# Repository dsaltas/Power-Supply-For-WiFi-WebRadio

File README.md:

## Power Supply For WiFi WebRadio

This is a miniature power supply with built-in Li-Ion charger for [WiFi WebRadio](https://github.com/dsaltas/WiFi-WebRadio).

It is based on [LTC3440](https://www.analog.com/en/products/ltc3440.html) chip. A Micropower Synchronous Buck-Boost DC/DC Converter.

### Features

- Voltage input 2,7V to 4,2V
- Voltage output 3,3V at 600mA
- Low battery LED indicator at 3V or less
- Li-Ion charger at 4,2V / 500mA

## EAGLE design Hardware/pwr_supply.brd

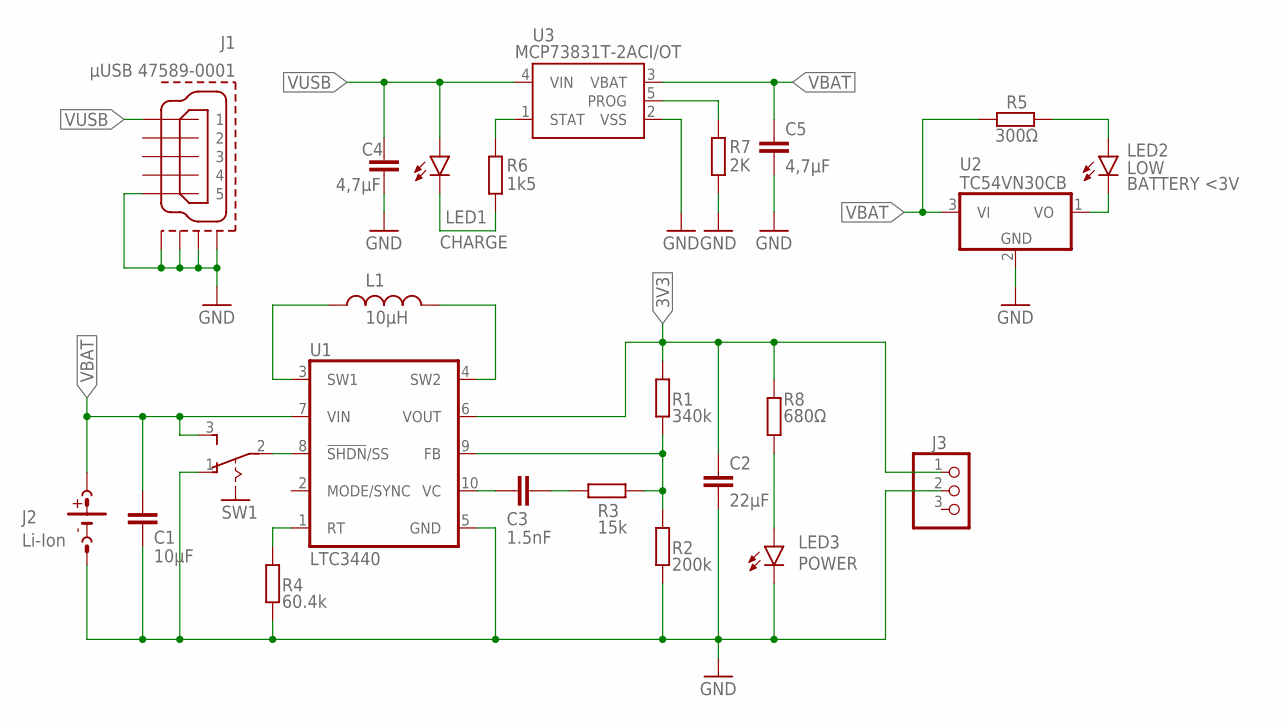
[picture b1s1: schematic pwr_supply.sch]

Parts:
C1: 10μF; C0805
C2: 22μF; C1210
C3: 1.5nF; C0805
C4, C5: 4,7μF; C0805
J1: μUSB 47589-0001; 47589-0001
J2: Li-Ion; JSTPH2
J3: PINHD-1X3/90; 1X03/90
L1: 10μH; CDRH6D38
LED1: CHARGE; CHIPLED_0805
LED2: LOW; CHIPLED_0805
LED3: POWER; CHIPLED_0805
R1: 340k; R0805
R2: 200k; R0805
R3: 15k; R0805
R4: 60.4k; R0805
R5: 300Ω; R0805
R6: 1k5; R0805
R7: 2K; R0805
R8: 680Ω; R0805
SW1: JS102011SAQN
U1: LTC3440; MSOP10
U2: TC54VN30CB; SOT23
U3: MCP73831T-2ACI/OT; SOT23-5

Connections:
3V3: C2.1, J3.1, R1.2, R8.2, U1.6 (VOUT)
GND: C1.2, C2.2, C4.2, C5.2, J1.5, J1.CASING1 (GND1), J1.CASING2 (GND2), J1.CASING3 (GND3), J1.CASING4 (GND4), J2.1 (-), J3.2, LED3.C, R2.1, R4.1, R7.1, SW1.1 (O), U1.5 (GND), U2.2 (GND), U3.2 (VSS)
unnamed: R4.2, U1.1 (RT)
unnamed: LED2.A, R5.1
unnamed: L1.1, U1.3 (SW1)
unnamed: L1.2, U1.4 (SW2)
unnamed: C3.1, U1.10 (VC)
unnamed: C3.2, R3.1
unnamed: R1.1, R2.2, R3.2, U1.9 (FB)
unnamed: SW1.2, U1.8 (!SHDN!/SS)
unnamed: LED2.C, U2.1 (VO)
unnamed: R7.2, U3.5 (PROG)
unnamed: R6.2, U3.1 (STAT)
unnamed: LED1.C, R6.1
unnamed: LED3.A, R8.1
VBAT: C1.1, C5.1, J2.2 (+), R5.2, SW1.3 (S), U1.7 (VIN), U2.3 (VI), U3.3 (VBAT)
VUSB: C4.1, J1.1, LED1.A, U3.4 (VIN)

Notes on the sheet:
BATTERY <3V

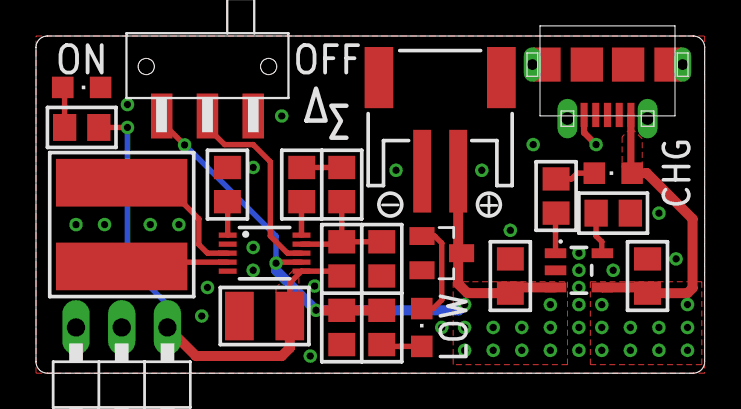
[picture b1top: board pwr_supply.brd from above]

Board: 2 copper layers, 37.1 x 18.7 mm, 24 parts (0 on the bottom side), 17 nets.

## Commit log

2020-03-13 Create test
2021-04-26 Bill of Materials
2021-04-26 Create keep

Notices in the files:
Hardware/pwr_supply.brd:
© 2019
parts and their libraries:
con-molex-usb: (C) 2014 Tomasz Boleslaw CEDRO, cederom@tlen.pl, http://www.tomek.cedro.info.
SparkFun-IC-Power: Licensing: Creative Commons ShareAlike 4.0 International - https://creativecommons.org/licenses/by-sa/4.0
